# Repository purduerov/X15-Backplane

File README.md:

# Readme for X15-Backplane

Whenever you make a new part, download the datasheet and save it here _**and**_ with the part in the parts library

Always pull other people's changes before beginning to work
`git pull`

Be sure to push your changes after  working on them. Run:
1. `git add .` to add any files in this directory or a subdirectory
or `git add -u` to add any modified files
2. (Optional) `git clean -nX` to see what ignored files can be removed
	`git clean -fX` removes ignored files (Eagle backups)
3. `git commit -m "helpful commit message"` with a description of the work that you did
4. `git push` to push your work to github

Other helpful commands
* `git status` says information about modified and staged files
* `git log` shows the recent commits of the repository
* `git log filename.extension` show the recent commits for just that file
* `git checkout first-couple-letter-of-commit-id` lets you go back to a previous version
* `git checkout master` brings you back to the latest commit
* `git tag` lists the tags
* `git tag -a orderX -m "the version of the board placed for the X'th order"` tag a specific commit
* `git push --tags` needed to push tags to remote
* `git show orderX` show the commit log for the given tag
* `git checkout orderX` go back and interact with the files at the tagged commit

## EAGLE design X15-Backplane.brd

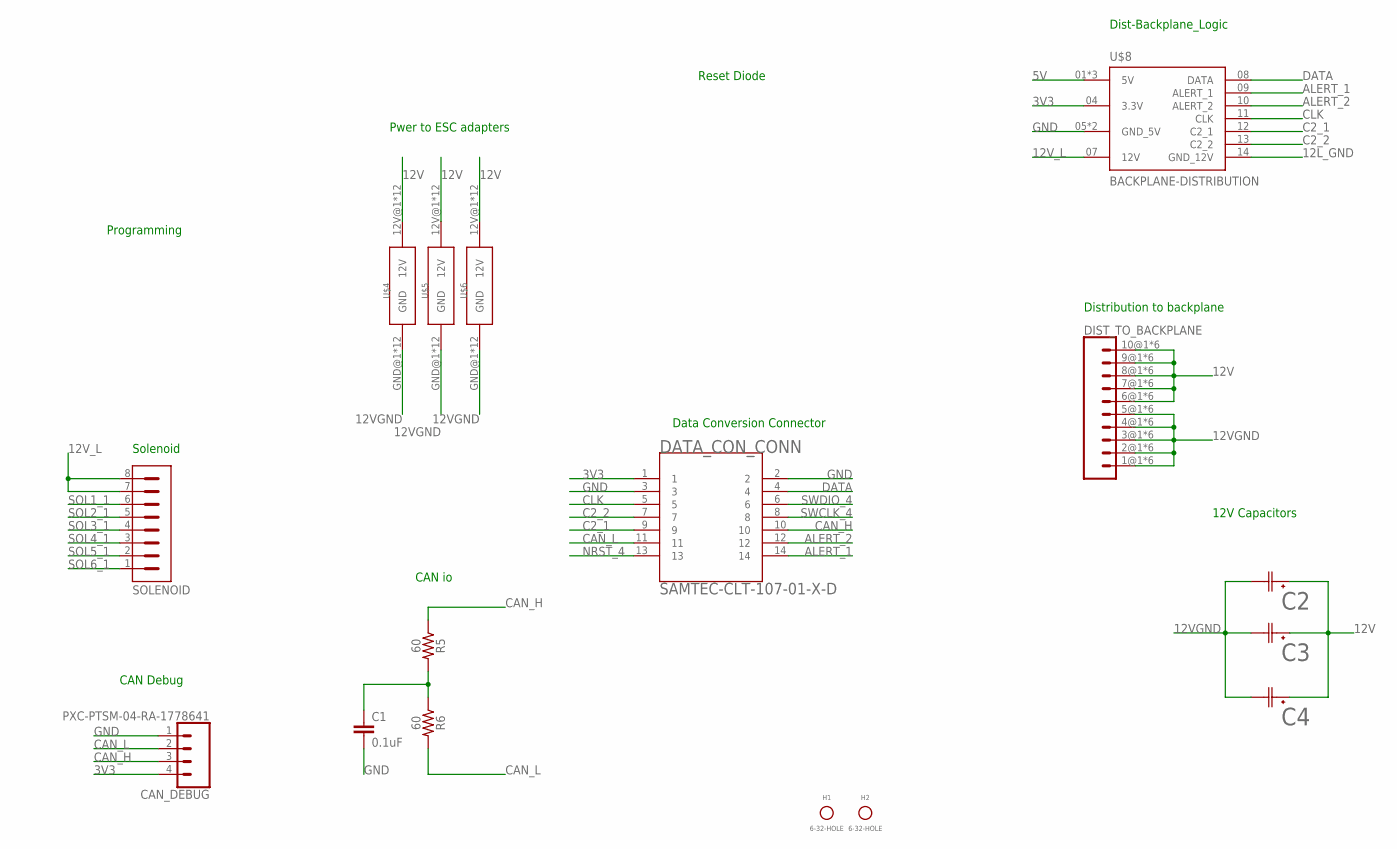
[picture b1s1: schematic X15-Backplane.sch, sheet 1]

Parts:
C1: 0.1uF; 0603
C2, C3, C4: UCV1E561MNL1GSCAP_UCD_8X10_NCH; CAP_UCD_8X10_NCH
CAN_DEBUG: PXC-PTSM-04-RA-1778641
DATA_CON_CONN: BACKPLANE->DATACONV; SAMTEC-CLT-107-01-X-D-BACKPLANE
DIST_TO_BACKPLANE: MPPT-10-01-01-L-RA-SD
H1, H2: 6-32-HOLE
R5, R6: 60; 0603
SOLENOID: PXC-8-RA-1778683
U$4, U$5, U$6: BACKPLANE_ESC_ADAPTER_PWRBKP; BACKPLANE_ESC_ADAPTER_BKP_PWR
U$8: BACKPLANE-DISTRIBUTION; SAMTEC_IPL1-107-01-X-D-K(B-D)

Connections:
3V3: CAN_DEBUG.4, DATA_CON_CONN.1, U$8.04 (3.3V); also elsewhere on the board
5V: U$8.01 (5V), U$8.02 (5V), U$8.03 (5V); also elsewhere on the board
12L_GND: U$8.14 (GND_12V); also elsewhere on the board
12V: C2.1, C3.1, C4.1, DIST_TO_BACKPLANE.6@1 (6), DIST_TO_BACKPLANE.6@2 (6), DIST_TO_BACKPLANE.6@3 (6), DIST_TO_BACKPLANE.6@4 (6), DIST_TO_BACKPLANE.6@5 (6), DIST_TO_BACKPLANE.6@6 (6), DIST_TO_BACKPLANE.7@1 (7), DIST_TO_BACKPLANE.7@2 (7), DIST_TO_BACKPLANE.7@3 (7), DIST_TO_BACKPLANE.7@4 (7), DIST_TO_BACKPLANE.7@5 (7), DIST_TO_BACKPLANE.7@6 (7), DIST_TO_BACKPLANE.8@1 (8), DIST_TO_BACKPLANE.8@2 (8), DIST_TO_BACKPLANE.8@3 (8), DIST_TO_BACKPLANE.8@4 (8), DIST_TO_BACKPLANE.8@5 (8), DIST_TO_BACKPLANE.8@6 (8), DIST_TO_BACKPLANE.9@1 (9), DIST_TO_BACKPLANE.9@2 (9), DIST_TO_BACKPLANE.9@3 (9), DIST_TO_BACKPLANE.9@4 (9), DIST_TO_BACKPLANE.9@5 (9), DIST_TO_BACKPLANE.9@6 (9), DIST_TO_BACKPLANE.10@1 (10), DIST_TO_BACKPLANE.10@2 (10), DIST_TO_BACKPLANE.10@3 (10), DIST_TO_BACKPLANE.10@4 (10), DIST_TO_BACKPLANE.10@5 (10), DIST_TO_BACKPLANE.10@6 (10), U$4.12V@1 (12V), U$4.12V@2 (12V), U$4.12V@3 (12V), U$4.12V@4 (12V), U$4.12V@5 (12V), U$4.12V@6 (12V), U$4.12V@7 (12V), U$4.12V@8 (12V), U$4.12V@9 (12V), U$4.12V@10 (12V), U$4.12V@11 (12V), U$4.12V@12 (12V), U$5.12V@1 (12V), U$5.12V@2 (12V), U$5.12V@3 (12V), U$5.12V@4 (12V), U$5.12V@5 (12V), U$5.12V@6 (12V), U$5.12V@7 (12V), U$5.12V@8 (12V), U$5.12V@9 (12V), U$5.12V@10 (12V), U$5.12V@11 (12V), U$5.12V@12 (12V), U$6.12V@1 (12V), U$6.12V@2 (12V), U$6.12V@3 (12V), U$6.12V@4 (12V), U$6.12V@5 (12V), U$6.12V@6 (12V), U$6.12V@7 (12V), U$6.12V@8 (12V), U$6.12V@9 (12V), U$6.12V@10 (12V), U$6.12V@11 (12V), U$6.12V@12 (12V); also elsewhere on the board
12VGND: C2.2, C3.2, C4.2, DIST_TO_BACKPLANE.1@1 (1), DIST_TO_BACKPLANE.1@2 (1), DIST_TO_BACKPLANE.1@3 (1), DIST_TO_BACKPLANE.1@4 (1), DIST_TO_BACKPLANE.1@5 (1), DIST_TO_BACKPLANE.1@6 (1), DIST_TO_BACKPLANE.2@1 (2), DIST_TO_BACKPLANE.2@2 (2), DIST_TO_BACKPLANE.2@3 (2), DIST_TO_BACKPLANE.2@4 (2), DIST_TO_BACKPLANE.2@5 (2), DIST_TO_BACKPLANE.2@6 (2), DIST_TO_BACKPLANE.3@1 (3), DIST_TO_BACKPLANE.3@2 (3), DIST_TO_BACKPLANE.3@3 (3), DIST_TO_BACKPLANE.3@4 (3), DIST_TO_BACKPLANE.3@5 (3), DIST_TO_BACKPLANE.3@6 (3), DIST_TO_BACKPLANE.4@1 (4), DIST_TO_BACKPLANE.4@2 (4), DIST_TO_BACKPLANE.4@3 (4), DIST_TO_BACKPLANE.4@4 (4), DIST_TO_BACKPLANE.4@5 (4), DIST_TO_BACKPLANE.4@6 (4), DIST_TO_BACKPLANE.5@1 (5), DIST_TO_BACKPLANE.5@2 (5), DIST_TO_BACKPLANE.5@3 (5), DIST_TO_BACKPLANE.5@4 (5), DIST_TO_BACKPLANE.5@5 (5), DIST_TO_BACKPLANE.5@6 (5), U$4.GND@1 (GND), U$4.GND@2 (GND), U$4.GND@3 (GND), U$4.GND@4 (GND), U$4.GND@5 (GND), U$4.GND@6 (GND), U$4.GND@7 (GND), U$4.GND@8 (GND), U$4.GND@9 (GND), U$4.GND@10 (GND), U$4.GND@11 (GND), U$4.GND@12 (GND), U$5.GND@1 (GND), U$5.GND@2 (GND), U$5.GND@3 (GND), U$5.GND@4 (GND), U$5.GND@5 (GND), U$5.GND@6 (GND), U$5.GND@7 (GND), U$5.GND@8 (GND), U$5.GND@9 (GND), U$5.GND@10 (GND), U$5.GND@11 (GND), U$5.GND@12 (GND), U$6.GND@1 (GND), U$6.GND@2 (GND), U$6.GND@3 (GND), U$6.GND@4 (GND), U$6.GND@5 (GND), U$6.GND@6 (GND), U$6.GND@7 (GND), U$6.GND@8 (GND), U$6.GND@9 (GND), U$6.GND@10 (GND), U$6.GND@11 (GND), U$6.GND@12 (GND)
12V_L: SOLENOID.7, SOLENOID.8, U$8.07 (12V); also elsewhere on the board
ALERT_1: DATA_CON_CONN.14, U$8.09 (ALERT_1)
ALERT_2: DATA_CON_CONN.12, U$8.10 (ALERT_2)
C2_1: DATA_CON_CONN.9, U$8.12 (C2_1)
C2_2: DATA_CON_CONN.7, U$8.13 (C2_2)
CAN_H: CAN_DEBUG.3, DATA_CON_CONN.10, R5.1; also elsewhere on the board
CAN_L: CAN_DEBUG.2, DATA_CON_CONN.11, R6.2; also elsewhere on the board
CLK: DATA_CON_CONN.5, U$8.11 (CLK)
DATA: DATA_CON_CONN.4, U$8.08 (DATA)
GND: C1.2, CAN_DEBUG.1, DATA_CON_CONN.2, DATA_CON_CONN.3, U$8.05 (GND_5V), U$8.06 (GND_5V); also elsewhere on the board
unnamed: C1.1, R5.2, R6.1
NRST_4: DATA_CON_CONN.13
SOL1_1: SOLENOID.6; also elsewhere on the board
SOL2_1: SOLENOID.5; also elsewhere on the board
SOL3_1: SOLENOID.4; also elsewhere on the board
SOL4_1: SOLENOID.3; also elsewhere on the board
SOL5_1: SOLENOID.2; also elsewhere on the board
SOL6_1: SOLENOID.1; also elsewhere on the board
SWCLK_4: DATA_CON_CONN.8
SWDIO_4: DATA_CON_CONN.6

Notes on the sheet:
Programming
Distribution to backplane
Dist-Backplane_Logic
Pwer to ESC adapters
Reset Diode
Solenoid
12V Capacitors
CAN io
CAN Debug
Data Conversion Connector

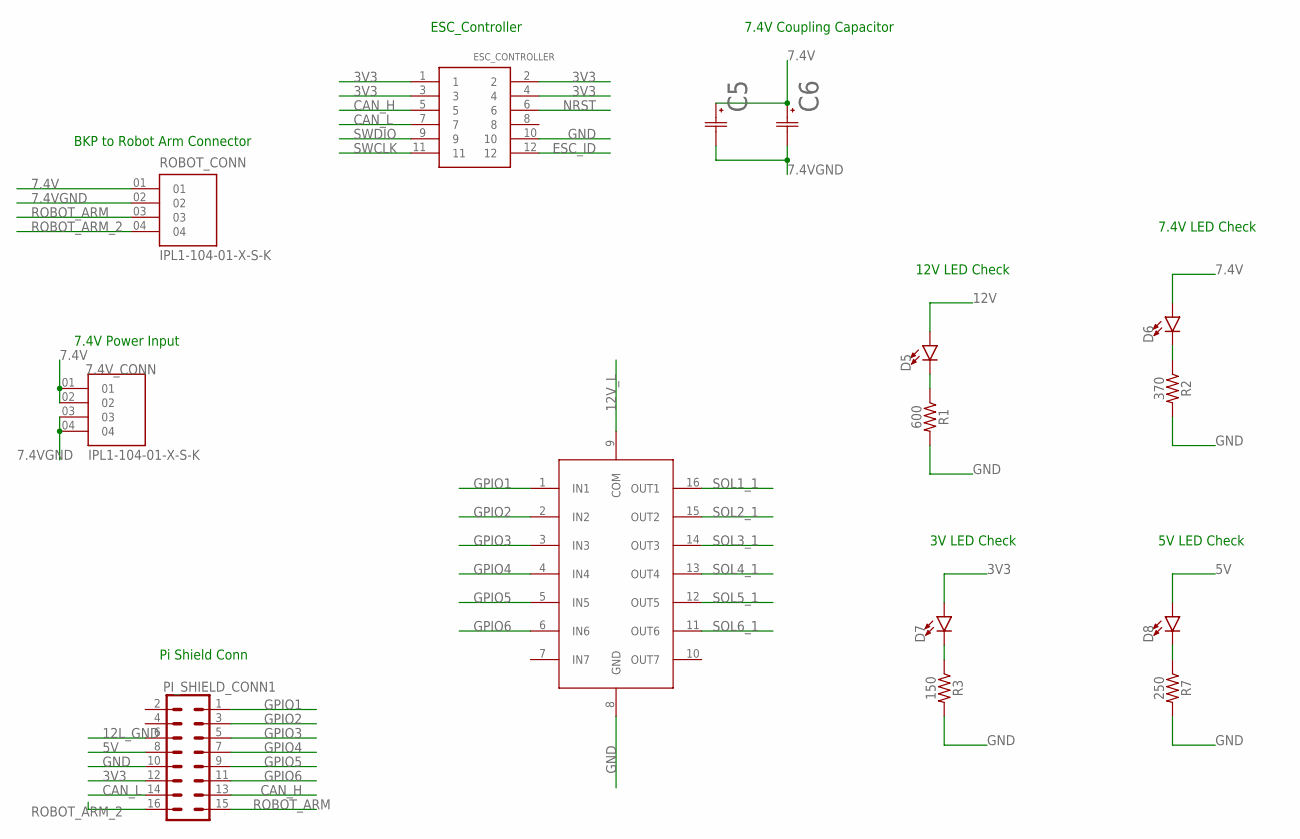
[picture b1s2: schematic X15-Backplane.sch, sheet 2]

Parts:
7.4V_CONN: IPL1-104-01-X-S-K; SAMTEC_IPL1-104-01-X-S-K
C5, C6: UCV1E561MNL1GSCAP_UCD_8X10_NCH; CAP_UCD_8X10_NCH
D5, D6, D7, D8: LED0603; LED-0603
ESC_CONTROLLER: BACKPLANE_CONNECTORSBKP; BACKPLANE_CONNECTORS_BKP
PI_SHIELD_CONN1: 8X_CONN; IPL7X2
R1: 600; 0603
R2: 370; 0603
R3: 150; 0603
R7: 250; 0603
ROBOT_CONN: IPL1-104-01-X-S-K; SAMTEC_IPL1-104-01-X-S-K
U1: ULN2003AD; 16-SOIC

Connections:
3V3: D7.A, ESC_CONTROLLER.1, ESC_CONTROLLER.2, ESC_CONTROLLER.3, ESC_CONTROLLER.4, PI_SHIELD_CONN1.12 (23); also elsewhere on the board
5V: D8.A, PI_SHIELD_CONN1.8 (19); also elsewhere on the board
7.4V: 7.4V_CONN.01, 7.4V_CONN.02, C5.1, C6.1, D6.A, ROBOT_CONN.01
7.4VGND: 7.4V_CONN.03, 7.4V_CONN.04, C5.2, C6.2, ROBOT_CONN.02
12L_GND: PI_SHIELD_CONN1.6 (17); also elsewhere on the board
12V: D5.A; also elsewhere on the board
12V_L: U1.9 (COM); also elsewhere on the board
CAN_H: ESC_CONTROLLER.5, PI_SHIELD_CONN1.13 (1); also elsewhere on the board
CAN_L: ESC_CONTROLLER.7, PI_SHIELD_CONN1.14 (2); also elsewhere on the board
ESC_ID: ESC_CONTROLLER.12
GND: ESC_CONTROLLER.10, PI_SHIELD_CONN1.10 (21), R1.2, R2.2, R3.2, R7.2, U1.8 (GND); also elsewhere on the board
GPIO1: PI_SHIELD_CONN1.1 (14), U1.1 (IN1)
GPIO2: PI_SHIELD_CONN1.3 (16), U1.2 (IN2)
GPIO3: PI_SHIELD_CONN1.5 (18), U1.3 (IN3)
GPIO4: PI_SHIELD_CONN1.7 (20), U1.4 (IN4)
GPIO5: PI_SHIELD_CONN1.9 (22), U1.5 (IN5)
GPIO6: PI_SHIELD_CONN1.11 (24), U1.6 (IN6)
unnamed: D6.C, R2.1
unnamed: D5.C, R1.1
unnamed: D7.C, R3.1
unnamed: D8.C, R7.1
NRST: ESC_CONTROLLER.6
ROBOT_ARM: PI_SHIELD_CONN1.15 (4), ROBOT_CONN.03
ROBOT_ARM_2: PI_SHIELD_CONN1.16 (3), ROBOT_CONN.04
SOL1_1: U1.16 (OUT1); also elsewhere on the board
SOL2_1: U1.15 (OUT2); also elsewhere on the board
SOL3_1: U1.14 (OUT3); also elsewhere on the board
SOL4_1: U1.13 (OUT4); also elsewhere on the board
SOL5_1: U1.12 (OUT5); also elsewhere on the board
SOL6_1: U1.11 (OUT6); also elsewhere on the board
SWCLK: ESC_CONTROLLER.11
SWDIO: ESC_CONTROLLER.9

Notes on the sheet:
ESC_Controller
7.4V LED Check
7.4V Coupling Capacitor
Pi Shield Conn
BKP to Robot Arm Connector
7.4V Power Input
12V LED Check
3V LED Check
5V LED Check

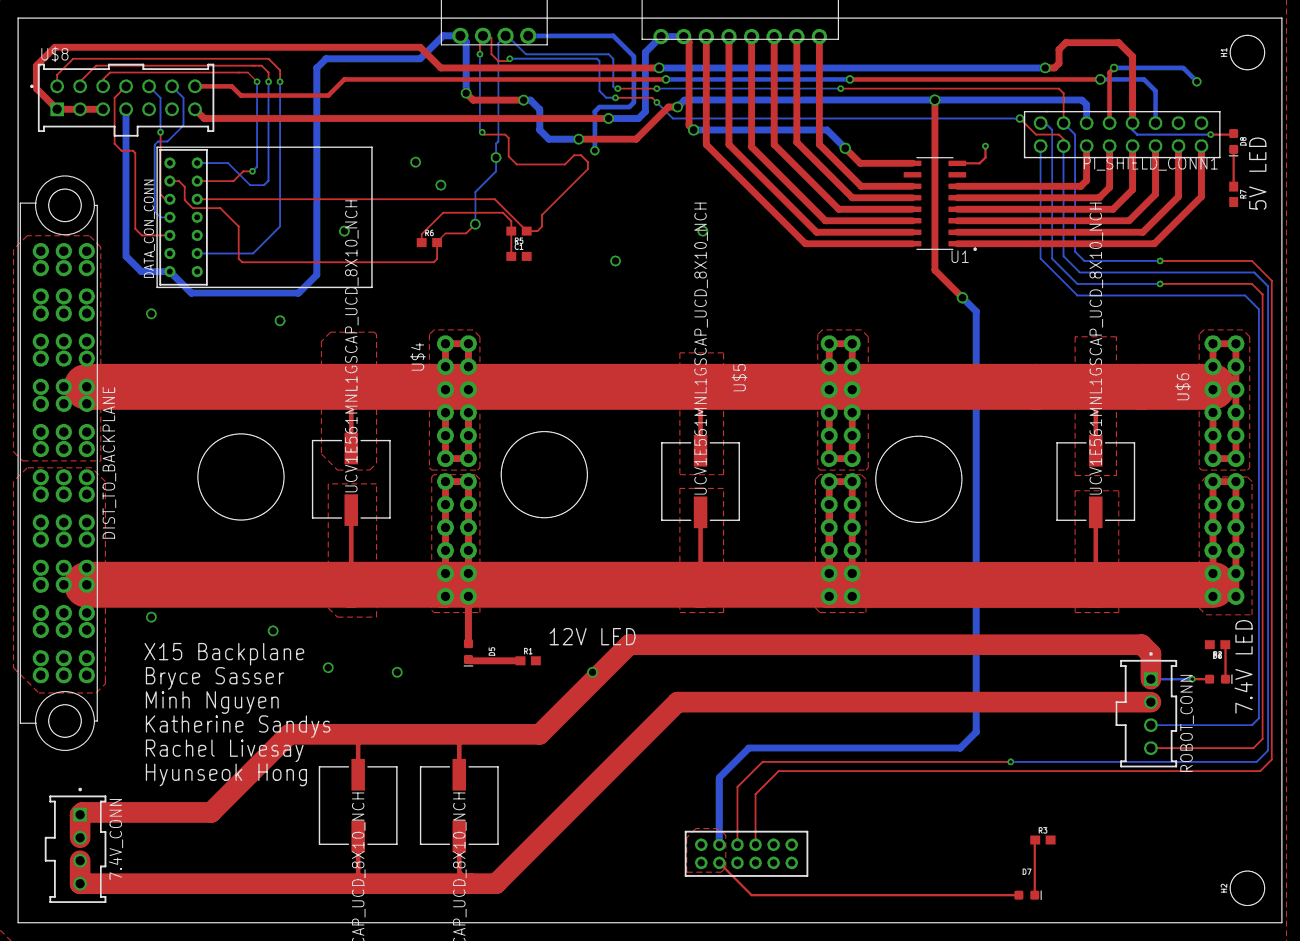
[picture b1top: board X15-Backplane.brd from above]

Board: 2 copper layers, 139.7 x 100.0 mm, 31 parts (0 on the bottom side), 36 nets.

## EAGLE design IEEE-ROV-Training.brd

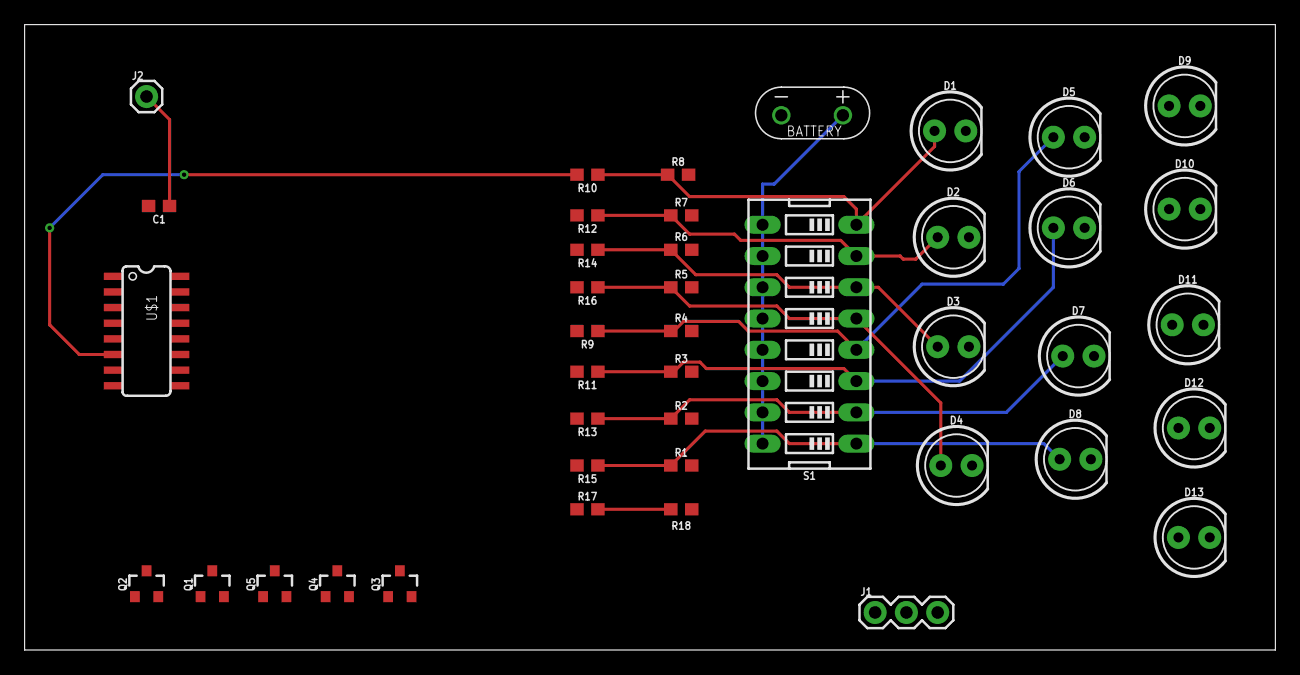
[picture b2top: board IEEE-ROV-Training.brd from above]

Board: 2 copper layers, 101.6 x 50.8 mm, 42 parts (0 on the bottom side), 31 nets.

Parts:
C1: 0.1uF; 0603
D1, D2, D3, D4, D5, D6, D7, D8, D9, D10, D11, D12, D13: LED_5MM
J1: 1X03
J2: 1X01
Q1, Q2, Q3, Q4, Q5: SOT23-3
R1, R2, R3, R4, R5, R6, R7, R8, R18: 10k; 0603
R9, R10, R11, R12, R13, R14, R15, R16, R17: 51; 0603
S1: DIPSWITCH-08
U$1: CD74HC283; SO016
U$2: AAA_BATTERIES; WIRE_LEADS

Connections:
3.3V: C1.1, D9.A, D10.A, D11.A, D12.A, D13.A, J2.1, U$1.16
A0: D5.A, R4.1, R9.1, S1.4
A1: D6.A, R3.1, R11.1, S1.3
A2: D7.A, R2.1, R13.1, S1.2
A3: D8.A, R1.1, R15.1, S1.1
B0: D1.A, R8.1, R10.1, S1.8
B1: D2.A, R7.1, R12.1, S1.7
B2: D3.A, R6.1, R14.1, S1.6
B3: D4.A, R5.1, R16.1, S1.5
CIN: J1.1, R17.1
COUT: J1.3, Q5.1, U$1.9
GND: C1.2, D1.K, D2.K, D3.K, D4.K, D5.K, D6.K, D7.K, D8.K, J1.2, Q1.2, Q2.2, Q3.2, Q4.2, Q5.2, R1.2, R2.2, R3.2, R4.2, R5.2, R6.2, R7.2, R8.2, R18.1, U$1.8, U$2.P$1
unnamed: R10.2, U$1.6
unnamed: R12.2, U$1.2
unnamed: R13.2, U$1.14
unnamed: R15.2, U$1.12
unnamed: R17.2, R18.2, U$1.7
unnamed: R14.2, U$1.15
unnamed: R9.2, U$1.5
unnamed: R16.2, U$1.11
unnamed: R11.2, U$1.3
unnamed: D9.K, Q1.3
unnamed: D10.K, Q2.3
unnamed: D11.K, Q3.3
unnamed: D12.K, Q4.3
unnamed: D13.K, Q5.3
unnamed: Q1.1, U$1.4
unnamed: Q2.1, U$1.1
unnamed: Q3.1, U$1.13
unnamed: Q4.1, U$1.10
VCC: S1.9, S1.10, S1.11, S1.12, S1.13, S1.14, S1.15, S1.16, U$2.P$2

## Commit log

2022-09-24 Hello
2022-10-15 Sorry for not pushing regularly
2022-10-22 Backplane
2022-10-22 Two Sheets
2022-10-22 Library Fixed
2022-10-22 LED Added
2022-10-22 board dimensions
2022-11-11 Final
2022-11-11 Minor chnages to clean up some traces
2022-11-11 12V Wire Fixed
2022-12-08 clearance fixed
2022-12-22 fixed dimensions
2023-01-03 Capacitor Changed
2023-01-12 Polygon finished
2023-01-24 ESC Fixed

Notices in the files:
parts and their libraries:
SparkFun-Capacitors: Licensing: Creative Commons ShareAlike 4.0 International - https://creativecommons.org/licenses/by-sa/4.0
COPYRIGHT: Copyright (C) 2023 Ultra Librarian. All rights reserved.
